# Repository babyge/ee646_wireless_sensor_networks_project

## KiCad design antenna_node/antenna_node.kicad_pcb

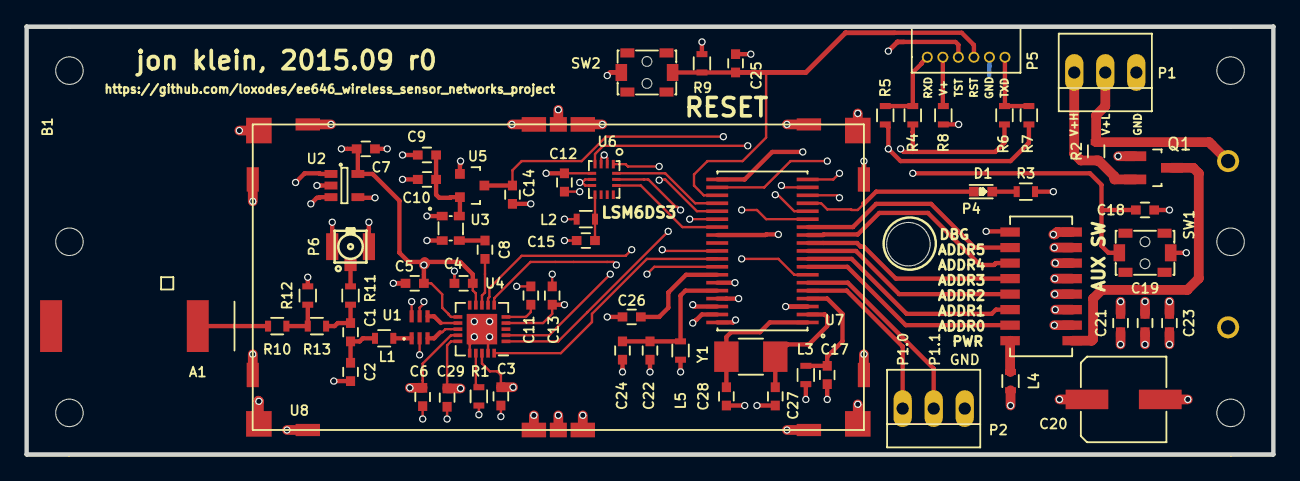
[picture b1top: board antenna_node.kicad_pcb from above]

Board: 4 copper layers, 102.0 x 35.0 mm, 67 parts (1 on the bottom side), 58 nets.

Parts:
A1: Antenna_2port; ANT1204LL05R0915A
B1: 1555C2F22GY; 1555CF22
C1, C23: 100 pF NPO; C_0603
C2: 1.8 pF; C_0603
C3, C4, C5, C6, C7, C8, C9, C11, C12, C13, C14, C15, C17, C19, C24, C29: 100 nF; C_0603
C10, C22: 1000 nF; C_0603
C18, C21, C25: 1 nF; C_0603
C20: 220 uF; CAP_POL_6p60mm
C26: 470 nF; C_0603
C27, C28: 10 pF; C_0603
D1: RED; LED-0603
L1: 5.6 nH; R_0603
L2, L3, L4, L5: 2.2 kOhm; R_0603
P1, P2: CONN_01X03; PINHEAD1-3
P3: CONN_01X02; BC2AAPC
P4: DIL16; CHS-08TA
P5: CONN_01X06; LPPB061NGCN-RC
P6: CONN_01X03; U.FL-COAX
Q1: Q_PMOS_GDS; SOT-23_Handsoldering
R1, R3, R9: 56k; R_0603
R2: 1; R_0603
R4, R5, R6, R7, R10, R13: 0; R_0603
R8, R11, R12: DNP; R_0603
SW1, SW2: SW_PUSH; PTS820J20MSMTRLFS
U1: 0896BM15A0001; 0896BM15A0001E
U2: TC77; SOT-23-5
U3: TCXO; NT2016SA
U4: CC110L; QFN-20-1EP_4x4mm_Pitch0.5mm
U5: MCP1700; SOT-23
U6: LSM6DS3; ST_LGA_14
U7: MSP430FR5739; TSSOP_38_Pitch0.65mm
U8: S01-50250500
Y1: Crystal_Small; R_1210_HandSoldering

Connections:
/AUXLED0: D1.1, U7.16
/AUXSW0: C18.1, SW1.1, U7.17
/CC_CSn: U4.7, U7.29
/CC_GDO: U4.6, U7.7
/CC_SCLK: U4.1, U7.25
/CC_SI: U4.20, U7.30
/CC_SO: U4.2, U7.31
/LSM_CS: U6.12, U7.26
/LSM_INT1: U6.4, U7.18
/LSM_MISO: U6.1, U7.24
/LSM_MOSI: U6.14, U7.23
/LSM_SCLK: U6.13, U7.14
/MCU_RXD: R4.2, R6.2, U7.20
/MCU_TXD: R5.2, R7.2, U7.19
/MSP_VCORE: C26.1, U7.32
/RST: C25.1, P5.4, R9.2, SW2.1, U7.22
/SWADDR0: P4.7, U7.8
/SWADDR1: P4.6, U7.9
/SWADDR2: P4.5, U7.10
/SWADDR3: P4.4, U7.11
/SWADDR4: P4.3, U7.12
/SWADDR5: P4.2, U7.13
/SWDEBUG: P4.1, U7.27
/TC_CS: U2.1, U7.36
/TC_SCK: U2.3, U7.35
/TC_SIO: U2.4, U7.37
/TST: P5.3, U7.21
/XTAL_EN: C14.1, U5.3, U7.15
GND: C2.2, C3.2, C4.2, C5.2, C6.2, C7.2, C9.2, C10.2, C11.2, C12.2, C13.2, C14.2, C15.2, C17.2, C18.2, C19.2, C20.2, C21.2, C22.2, C23.2, C24.2, C25.2, C26.2, C27.1, C28.1, C29.2, P1.1, P2.1, P3.2, P4.10, P4.11, P4.12, P4.13, P4.14, P4.15, P4.16, P5.5, P6.2, P6.3, Q1.1, R1.1, R3.2, R12.1, SW1.2, SW2.2, U1.2, U1.5, U1.6, U2.2, U3.1, U3.2, U4.16, U4.19, U4.21, U5.1, U6.2, U6.3, U6.6, U6.7, U7.3, U7.33, U7.38, U8.1, U8.2, U8.3, U8.4, U8.5, U8.6, U8.7, U8.8, U8.9, U8.10, U8.11, U8.12, U8.13, U8.14, U8.15, U8.16, U8.17, U8.18
unnamed: A1.1, R10.2
unnamed: C1.1, C2.1, L1.1
unnamed: C1.2, R11.1, R13.1
unnamed: C8.1, U4.8
unnamed: C8.2, U3.3
unnamed: C9.1, C10.1, U3.4, U5.2
unnamed: C11.1, U4.5
unnamed: C15.1, L2.1, U6.8
unnamed: C17.1, L3.1, U7.4
unnamed: C22.1, C24.1, L5.1, U7.34
unnamed: C27.2, U7.2, Y1.1
unnamed: C28.2, U7.1, Y1.2
unnamed: D1.2, R3.1
unnamed: L1.2, U1.1
unnamed: L4.1, P4.8
unnamed: P1.2, P3.1, R2.2
unnamed: P1.3, Q1.2, R2.1
unnamed: P2.2, U7.6
unnamed: P2.3, U7.5
unnamed: P4.9, Q1.3
unnamed: P5.1, R4.1, R5.1
unnamed: P5.2, R8.1
unnamed: P5.6, R6.1, R7.1
unnamed: P6.1, R11.2
unnamed: R1.2, U4.17
unnamed: R10.1, R12.2, R13.2
unnamed: U1.3, U4.13
unnamed: U1.4, U4.12
VCC: C3.1, C4.1, C5.1, C6.1, C7.1, C12.1, C13.1, C19.1, C20.1, C21.1, C23.1, C29.1, L2.2, L3.2, L4.2, L5.2, R8.2, R9.1, U2.5, U4.4, U4.9, U4.11, U4.14, U4.15, U4.18, U6.5

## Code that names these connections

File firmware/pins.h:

#define LEDOUT PJOUT
#define LEDDIR PJDIR
#define LED1 BIT1

// uart pins
#define UARTOUT P2OUT
#define UARTSEL P2SEL0
#define UARTDIR P2DIR
#define RXD (1 << 6)
#define TXD (1 << 5)

// switches and LEDs
#define SWADDR0_PIN (1 << 0)
#define SWADDR0_OUT P3OUT
#define SWADDR0_DIR P3DIR

#define SWADDR1_PIN (1 << 1)
#define SWADDR1_OUT P3OUT
#define SWADDR1_DIR P3DIR

#define SWADDR2_PIN (1 << 2)
#define SWADDR2_OUT P3OUT
#define SWADDR2_DIR P3DIR

#define SWADDR3_PIN (1 << 3)
#define SWADDR3_OUT P3OUT
#define SWADDR3_DIR P3DIR

#define SWADDR4_PIN (1 << 3)
#define SWADDR4_OUT P1OUT
#define SWADDR4_DIR P1DIR

#define SWADDR5_PIN (1 << 4)
#define SWADDR5_OUT P1OUT
#define SWADDR5_DIR P1DIR

#define SWDEBUG_PIN (1 << 5)
#define SWDEBUG_OUT P3OUT
#define SWDEBUG_DIR P3DIR

#define SWAUX0_PIN (1 << 2)
#define SWAUX0_OUT PJOUT
#define SWAUX0_DIR PJDIR

#define LED0_PIN (1 << 1)
#define LED0_OUT PJOUT
#define LED0_DIR PJDIR


// cc110L pins, SPI on UB0
#define CC_SCK_PIN (1 << 2)
#define CC_SCK_OUT P2OUT
#define CC_SCK_DIR P2DIR
#define CC_SCK_SEL P2SEL0

#define CC_MISO_PIN (1 << 7)
#define CC_MISO_OUT P1OUT
#define CC_MISO_DIR P1DIR
#define CC_MISO_SEL P1SEL0

#define CC_MOSI_PIN (1 << 6)
#define CC_MOSI_OUT P1OUT
#define CC_MOSI_DIR P1DIR
#define CC_MOSI_SEL P1SEL0

#define CC_CG0_OUT P1OUT
#define CC_CG0_PIN (1 << 2)
#define CC_CG0_DIR P1DIR

#define CC_CS_OUT P3OUT
#define CC_CS_DIR P3DIR
#define CC_CS_PIN (1 << 7)

#define CC_XTAL_OUT PJOUT
#define CC_XTAL_DIR PJDIR
#define CC_XTAL_PIN (1 << 0)

// tc77 pins, SPI is bitbanged
#define TC_OUT P2OUT
#define TC_DIR P2DIR
#define TC_SIO_PIN (1 << 4)
#define TC_CS_PIN (1 << 3)
#define TC_SCK_PIN (1 << 7)

// lsm6ds3 pins, SPI on UA0
#define LSM_INT1_OUT PJOUT
#define LSM_INT1_DIR PJDIR
#define LSM_INT1_SEL PJSEL0
#define LSM_INT1_PIN (1 << 3)

#define LSM_MISO 
#define LSM_MOSI_OUT P2OUT
#define LSM_MOSI_DIR P2DIR
#define LSM_MOSI_SEL P2SEL0
#define LSM_MOSI_PIN (1 << 0)

#define LSM_MISO_OUT P2OUT
#define LSM_MISO_DIR P2DIR
#define LSM_MISO_SEL P2SEL0
#define LSM_MISO_PIN (1 << 1)

#define LSM_CS_OUT P3OUT
#define LSM_CS_DIR P3DIR
#define LSM_CS_SEL P3SEL0
#define LSM_CS_PIN (1 << 4)

#define LSM_SCK_OUT P1OUT
#define LSM_SCK_DIR P1DIR
#define LSM_SCK_SEL P1SEL0
#define LSM_SCK_PIN (1 << 5)

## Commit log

2015-09-07 initial commit, schematic and footprints complete
2015-09-08 finished initial compomnent placement, added rf shield and enclosure
2015-09-08 finished most of layout, silkscreen cleanup and DFM remains..
2015-09-09 finished cleanup, ordered r0
2015-09-25 added working makefile for launchpad, added pin definitions
2015-10-05 started porting interrupt uart code, probably just not bother and just use busy wait version..
2015-10-11 added bsd licenced TI cc1101 library
2015-10-11 started modifying TI cc library for sensor node board
2015-10-11 modified TI bitbang spi driver for sclk on different port as si/so
2015-10-12 working on rf blinkenlights..
2015-10-12 added aclk off crystal
